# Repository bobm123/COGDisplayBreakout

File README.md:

# COG Display Breakout

This is a breakout board for the **ERC12864FSF-11** COG (Chip On Glass) LCD module, a 0.96", 128x64 pixel display using an ST7567 controller and 4-wire SPI an interface. The PCB routes the display's inputs from its 12-pin FFC cable to a breadboard-friendly 2.54mm pin header. It also exposes the backlight LED pins and provides a few discrete components for LCD module.

It was designed to have a  form factor (~27x27mm, 4 mounting holes, pin headers) to like the Adafruit [0.96" OLED module](https://www.adafruit.com/product/326) and similar 1" displays.

LCD technology differs from the OLED displays commonly found on display boards of this size. LCD should be daylight readable like e-paper, but with simpler hardware and software requirements. However, LCDs may need a backlight in low-light conditions, so the breakout includes connections display's built-in LED with an option for always on operation. Contrast control is through software.

## Specifications

| Parameter | Value |
|-----------|-------|
| Display | [ERC12864FSF-11](https://www.buydisplay.com/0-96-inch-low-cost-white-128x64-graphic-cog-lcd-display-st7567-spi) (128x64, monochrome) |
| Controller | ST7567 |
| Interface | 4-wire SPI |
| Supply voltage | 3.3V only |
| Board size | ~27 x 27mm |
| Mounting | 4x M2 holes |

## Repository Structure

```
ArduinoCode/                             Example sketches for ESP32-C3
COGDisplayBreakout.pretty/               Custom footprint library
COGDisplayBreakout.3dmodels/             Custom 3D models
docs/                                    Datasheets, reference designs, tutorials
images/                                  Image assets
step/                                    3D models of the board and a small case
COGDisplayBreakout.kicad_sch             Schematic
COGDisplayBreakout.kicad_pcb             PCB layout
COGDisplayBreakout.kicad_sym             Custom symbol library
README.md
```

---

## Schematic and Board Layout

The KiCad 9 project files are at the repository root.

### Circuit Overview

The schematic connects the ERC12864FSF-11 display to an 8-pin SPI header (J1) with supporting passives:

**Header pinout (J1 - SPI_Header):**

| Pin | Signal | Description |
|-----|--------|-------------|
| 1 | SDA | SPI data (MOSI) |
| 2 | SCL | SPI clock |
| 3 | A0 | Data/command select (DC) |
| 4 | /RST | Reset (active low) |
| 5 | /CS | Chip select (active low) |
| 6 | LED | LED control |
| 7 | VDD | +3.3V supply |
| 8 | GND | Ground |

**Passive components:**

| Ref | Value | Purpose |
|-----|-------|---------|
| R1 | 20R | Backlight LED current-limiting resistor |
| C1 | 10uF |  VDD bypass capacitor|
| C2 | 100nF | VDD bypass capacitor |
| C3 | 1uF | Charge pump capacitor (V0 to XV0) |
| C4 | 1uF | Charge pump capacitor (V0 to GND) |
| U1 | APX805S | Power-on reset IC for display /RST line |

The ST7567's built-in voltage booster generates the LCD bias voltage using external capacitors C3, and C4. No regulator or level shifting is included; the board is 3.3V only. Capacitors C1 and C2 are for decoupling. The R1 value was taken from the reference design, but for 10-20 mA LED current it should be about 200 Ohms.

The APX805S monitors VDD and holds the display /RST line low until power is stable, providing a clean power-on reset without requiring a GPIO pin from the host microcontroller. The /RST header pin (pin 4) is still available for external reset if needed.

### PCB

This is a 2-layer board, ~27x27mm. The display's 12-pin FFC cable (0.6mm pitch) is soldered directly to SMD pads on the back side. The display module mounts flat against the front by means of plastic mounting pins on the display case and the solder tabs for the backlight LED. Four M2 mounting holes at the corners matching similar OLED modules.

The display's 12-pin FFC cable is a non-standard 0.6mm pitch, so must be soldered directly to pads on the breakout PCB.

PCB Front (ground plane copper hidden)

PCB Back

### Board Revisions

- **V0.1** (March 2026) - Initial prototype. Known issues: C1 wiring error, missing VG capacitor. See `AssemblyNotes.txt` for workarounds.

- **V0.2** (March 2026) - Fixed capacitor circuit. Known issue: backlight A/K pads swapped. See `AssemblyNotes.txt`.
Gerber files: V0.2 in `Gerbers20260323/`.

- **V1.0** (April 2026) - Fixed A/K pads and connected LED control to pin 6. See `AssemblyNotes.txt`.
Gerber files: V1.0 in `Gerbers20260403/`.

- **V1.1** (April 2026) - Added APX805S power-on reset IC for display /RST line. External reset connection via header pin 4 remains optional.
Gerbers sent to DigiKey RedBoard fab 2026-04-15.

---

## Custom ERC12864FSF-11 KiCad Library

The project includes a custom schematic symbol, PCB footprint, and 3D model for the ERC12864FSF-11 display module. These are in project-local libraries referenced via `sym-lib-table` and `fp-lib-table`.

### Schematic Symbol

**File:** `COGDisplayBreakout.kicad_sym`
**Symbol name:** `ERC12864FSF-11`

12-pin FFC cable (0.6mm pitch, 19mm long) plus 2 backlight pins.

| Pin | Name | Type | Description |
|-----|------|------|-------------|
| 1 | ~{CS} | Input | Chip select (active low) |
| 2 | ~{RST} | Input | Reset (active low) |
| 3 | A0 | Input | Data/command select |
| 4 | SCL | Input | SPI clock |
| 5 | SDA | Input | SPI data (MOSI) |
| 6 | VDD | Power | +3.3V supply |
| 7 | VSS | Power | Ground |
| 8 | V0 | Passive | Contrast voltage (booster output) |
| 9 | XV0 | Passive | Booster capacitor tap |
| 10 | NC | - | Not connected |
| 11 | NC | - | Not connected |
| 12 | VG | Passive | Negative voltage for LCD bias |
| A | A | Passive | Backlight LED anode |
| K | K | Passive | Backlight LED cathode |

Note: The backlight pins (A, K) are separate solder tabs on the display module, not part of the 12-pin FFC cable.

### PCB Footprint

**File:** `COGDisplayBreakout.pretty/ERC12864FSF-11_COG_LCD.kicad_mod`

There is a lot going on with this component's footprint:
- 12 SMD pads at 0.6mm pitch for direct-solder FFC cable connection
- Module outline on front silkscreen
- Back silkscreen shows how the FFC cable would wrap around
- 2 through-hole oval pads for backlight pins (A and K)
- Two NPT holes for case aliment studs
- An NPT oval slot to pass the FFC cable to the back of the PCB 

The 12 SMD pads are a bit longer to allow some play when wrapping the FFC cable around to the back. The pads and oval slot are positioned relative to the stud holes and backlight pins so the FFC cable end is centered on the pads. 

Unfortunately, there does not seem to be an FFC/FPC connector available in 12-pin, 6mm pitch so it must be soldered to the PCB. A piece of Kapton tape over the solder joins will provide a bit of strain relief and protection from shorts. 
  
### 3D Model

**Directory:** `COGDisplayBreakout.3dmodels/`

| File | Format | Description |
|------|--------|-------------|
| `ERC12864FSF-11.step` | STEP | Solid body model for KiCad 3D viewer |
| `ERC12864FSF-11_COG_LCD.wrl` | VRML | Lightweight preview model |

The STEP model is referenced by the footprint and renders in KiCad's 3D viewer and to export the PCB with components as a 3D model.

---

## Arduino Code

Example sketches are in `ArduinoCode/`. The code should run on most modern Arduino board variants with sufficient pins and memory. The code currently targets the [**Adafruit QT Py ESP32-C3**](https://www.adafruit.com/product/5405) and uses the **U8g2** graphics library.

### Dependencies

- [U8g2](https://github.com/olikraus/u8g2) - Monochrome graphics library (handles ST7567 initialization, SPI transport, fonts, and drawing)
- SPI (built-in)

Install U8g2 via the Arduino IDE Library Manager.

### Pin Mapping (QT Py ESP32-C3 to breakout header)

| Display Signal | Header Pin | QT Py Pin | ESP32-C3 GPIO |
|----------------|------------|-----------|---------------|
| SCL (clock) | 1 | SCK | 10 |
| SDA (data) | 2 | MO | 7 |
| A0 (DC) | 3 | MI* | 8 |
| /RST | 4 | APX805S on breakout | - |
| /CS | 5 | tied to GND | - |
| LED | 6 | A3 | - |
| GND | 1 | GND | - |
| VDD | 2 | 3V3 | - |

*The MISO pin is repurposed as GPIO since the ERC12864 does not provide data out.

### Sketches

Here are some Arduino sketches that can be run on a XIAO style board like Adafruit's QT Py ESP32-C3 with the connections shown above

| Sketch | Description |
|--------|-------------|
| `ERC12864_Hello/` | Minimal hello-world with text and simple graphics. Also blinks the QT Py's NeoPixel. |
| `ERC12864_SPIDemo/` | AI Port of the manufacturer's C tutorial. Cycles through text, graphics primitives, XBM bitmap, and test patterns. Includes commented-out contrast adjustment code for future button support. |
| `GraphicsTest/` | U8g2 graphics test suite (from the U8g2 examples, configured for this display). |
| `ScrollingText/` | U8g2 scrolling text demo (from the U8g2 examples, configured for this display). |

### U8g2 Constructor

All sketches use the same U8g2 constructor. Identifies the display module by part number and the SPI interface pins. See mappings above.

```cpp
U8G2_ST7565_ERC12864_ALT_F_4W_SW_SPI u8g2(U8G2_R0,
    /* clock=*/ 10, /* data=*/ 7, /* cs=*/ U8X8_PIN_NONE, /* dc=*/ 8, /* reset=*/ U8X8_PIN_NONE);
```

- `ERC12864_ALT` - contrast-improved variant for this display
- `_F_` - full framebuffer mode (~1KB RAM)
- `4W_SW_SPI` - 4-wire software SPI

The 4-wire HW variants of the U8g2 constructors are intended for the platform's native SPI interface: MOSI, MISO, clock and chip select. Since this device is write only the MISO pin is repurposed for A0 (Data/Command select). The 4-wire SW constructor is used to support this pin mapping but others are possible.

/CS is tied to GND on the breakout board, so the display is always selected and no GPIO is needed for chip select. If sharing the SPI bus with other devices, connect /CS to a GPIO pin and replace `U8X8_PIN_NONE` with that pin number in the constructor.

/RST is managed by the on-board APX805S power-on reset IC, so no GPIO is needed for reset. If external reset control is required, connect the /RST header pin to a GPIO and replace the reset `U8X8_PIN_NONE` with that pin number.

---

## Reference Documentation

Datasheets and reference material are in `docs/`:

- `ERC12864-11_Datasheet.pdf` - Display module datasheet
- `ST7567_V1.7.pdf` - Controller IC datasheet
- `ERC12864FSF-11_Display.md` - Display specifications summary
- `ERC12864FSF-11_SPI_Reference_Design.md` - Wiring guide and U8g2 examples
- `ERC12864-11_Tutorial/` - Manufacturer's C code tutorial and interface schematic

## Tools

- **KiCad 9** for schematic and PCB design
- **Arduino IDE** with ESP32 board support for firmware development
- **U8g2** library for display graphics

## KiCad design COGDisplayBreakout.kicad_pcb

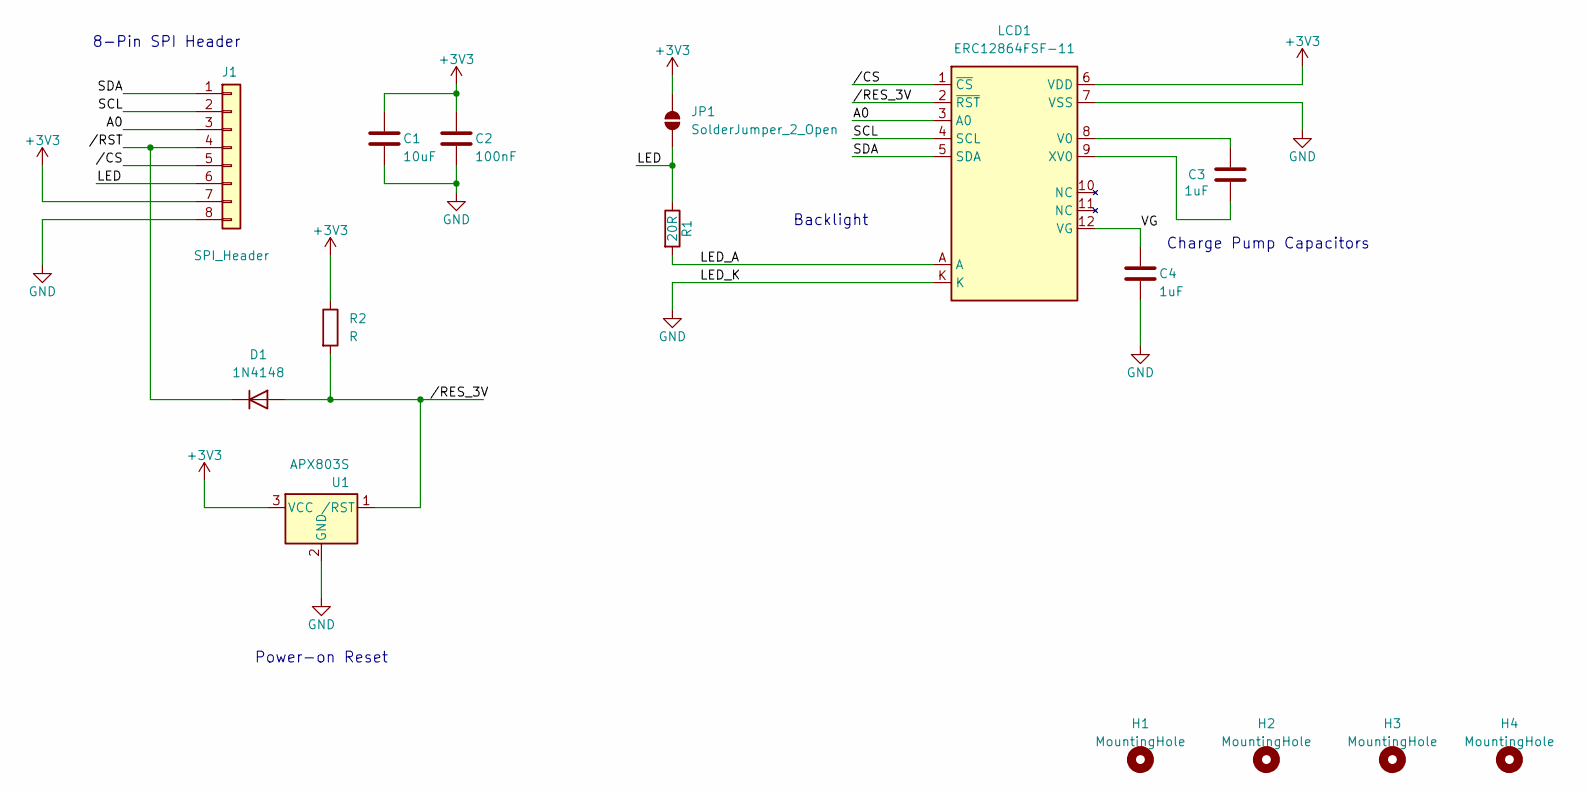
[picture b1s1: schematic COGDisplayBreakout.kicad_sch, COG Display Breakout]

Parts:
C1: 10uF; C_0805_2012Metric_Pad1.18x1.45mm_HandSolder
C2: 100nF; C_0805_2012Metric_Pad1.18x1.45mm_HandSolder
C3, C4: 1uF; C_0805_2012Metric_Pad1.18x1.45mm_HandSolder
D1: 1N4148; D_0805_2012Metric_Pad1.15x1.40mm_HandSolder
H1, H2, H3, H4: MountingHole; MountingHole_2.5mm
J1: SPI_Header; PinHeader_1x08_P2.54mm_Vertical
JP1: SolderJumper_2_Open; SolderJumper-2_P1.3mm_Open_RoundedPad1.0x1.5mm
LCD1: ERC12864FSF-11; ERC12864FSF-11_COG_LCD
R1: 20R; R_0805_2012Metric_Pad1.20x1.40mm_HandSolder
R2: R; R_0805_2012Metric_Pad1.20x1.40mm_HandSolder
U1: APX803S; TSOT-23

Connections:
+3V3: C1.1, C2.1, J1.7, JP1.2 (B), LCD1.6 (VDD), R2.1, U1.3 (VCC)
/A0: J1.3, LCD1.3 (A0)
/LED: J1.6, JP1.1 (A), R1.1
/LED_A: LCD1.A, R1.2
/SCL: J1.2, LCD1.4 (SCL)
/SDA: J1.1, LCD1.5 (SDA)
/VG: C4.1, LCD1.12 (VG)
//CS: J1.5, LCD1.1 (~CS)
//RES_3V: D1.2 (A), LCD1.2 (~RST), R2.2, U1.1 (/RST)
//RST: D1.1 (K), J1.4
GND: C1.2, C2.2, C4.2, J1.8, LCD1.7 (VSS), LCD1.K, U1.2 (GND)
unnamed: C3.1, LCD1.8 (V0)
unnamed: C3.2, LCD1.9 (XV0)

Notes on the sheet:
Charge Pump Capacitors
8-Pin SPI Header
Backlight
Power-on Reset

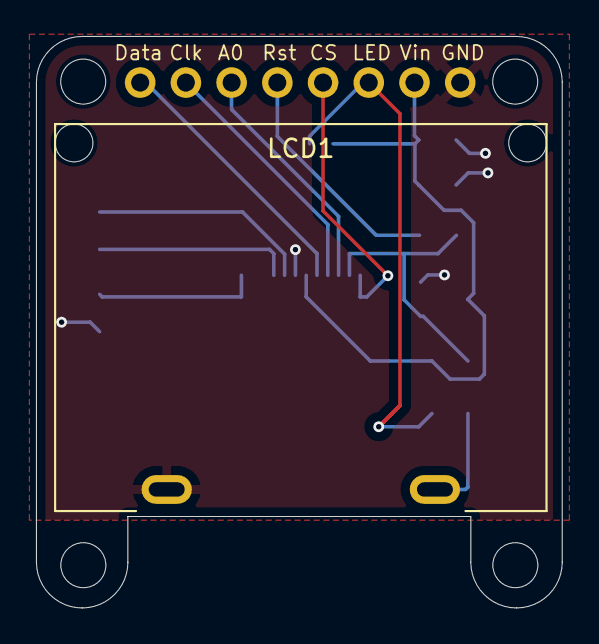
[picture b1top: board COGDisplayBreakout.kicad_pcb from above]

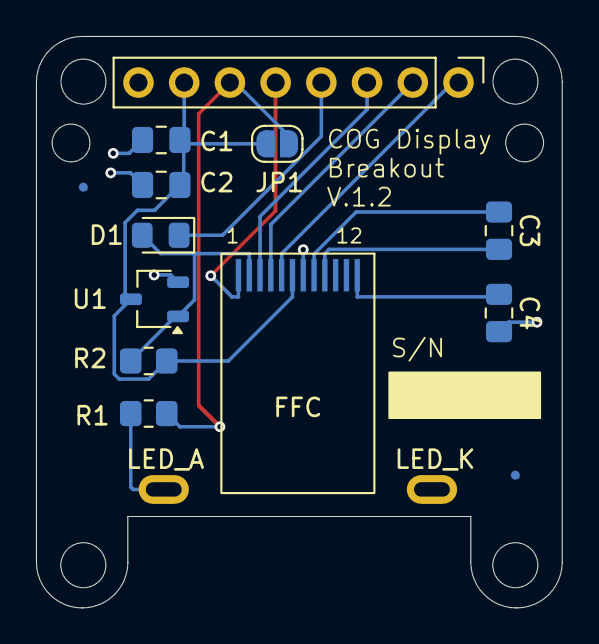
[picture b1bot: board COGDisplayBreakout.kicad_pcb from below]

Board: 2 copper layers, 29.2 x 31.8 mm, 17 parts (12 on the bottom side), 13 nets.

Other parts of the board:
FID1, FID2: FIDUCIAL""; Fiducial_0.5mm_Mask1.5mm

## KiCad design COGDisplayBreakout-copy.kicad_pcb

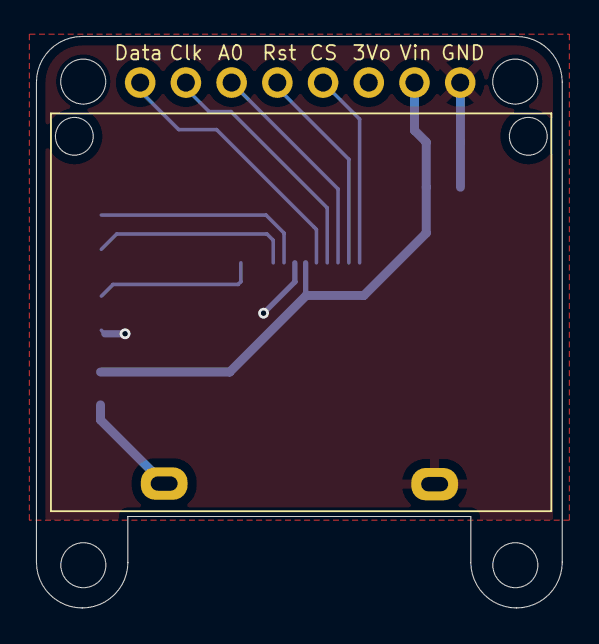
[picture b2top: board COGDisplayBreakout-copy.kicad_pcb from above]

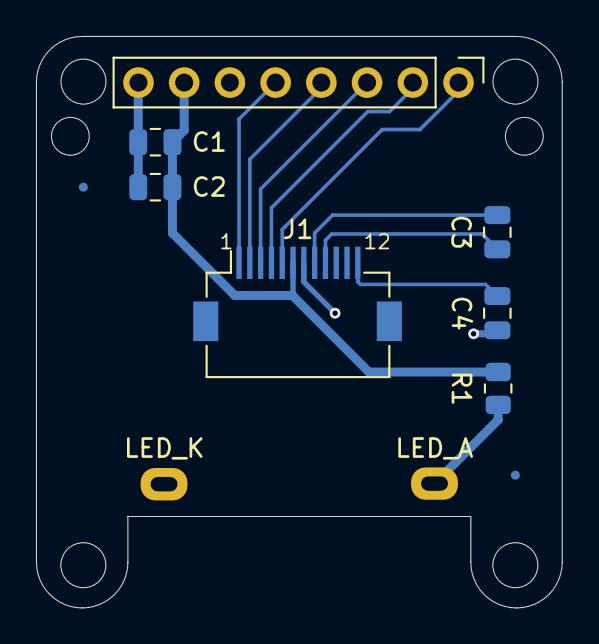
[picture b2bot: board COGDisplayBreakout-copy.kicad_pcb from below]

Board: 2 copper layers, 29.2 x 31.8 mm, 15 parts (11 on the bottom side), 11 nets.

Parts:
C1: 10uF; C_0805_2012Metric
C2: 100nF; C_0805_2012Metric
C3, C4: 1uF; C_0805_2012Metric
FID1, FID2: FIDUCIAL""; Fiducial_0.5mm_Mask1.5mm
H1, H2, H3, H4: MountingHole; MountingHole_2.5mm
J1: FPC_12pin; FFC_SolderPads12pos_x_0.60mm_Horizontal
J2: SPI_Header; PinHeader_1x08_P2.54mm_Vertical
J4, J5: Conn_01x01; PinHeader_1x01_P2.54mm_Oblong
R1: 20R; R_0805_2012Metric

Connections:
+3V3: C1.1, C2.1, J1.6, J2.7, R1.1
/A0: J1.3, J2.3
/LED_A: J4.1, R1.2
/SCL: J1.4, J2.2
/SDA: J1.5, J2.1
/V0: C3.1, J1.8
/VG: C4.1, J1.12
/XV0: C3.2, J1.9
//CS: J1.1, J2.5
//RST: J1.2, J2.4
GND: C1.2, C2.2, C4.2, J1.7, J2.8, J5.1

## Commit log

2026-03-04 Initial Commit of COG breakout board with SPI interface
2026-03-25 3rd Rev send to OshPark
2026-03-26 Adds a footprint and symbol for the ERC12864FSF-11
2026-03-26 Adds a 3D model for the ERC12864FSF-11
2026-03-26 Some adjustments to the ERC12864 3D model
2026-04-02 Notes on the v0.2 boards
2026-04-02 Adds a case based on v0.2 board outline
2026-04-02 Adds the gerbers for v0.2 and some example code
2026-04-02 Adds documentation from the BuyDisplay website
2026-04-02 Adds a readme
2026-04-02 Fixes v0.2 problems, new symbol and 3D model
2026-04-03 Rewired LED: fix A/K swap and adds control from pin 6
2026-04-03 Sent to fab 04/03/2026
2026-04-04 Ensure Handsolder 0805 footprints
2026-04-04 readme edits
2026-04-04 Fixes head pin names and adds some links
2026-04-04 passive refs and functions
2026-04-04 Adds a screen grab of schematic and PCB
2026-04-04 Readme edits and directory cleanup
2026-04-08 Adds a 3D model of a bezel
2026-04-12 Removes /CS line (tied low) from test code
2026-04-12 Adds power on reset
2026-04-12 Some project cleanup after a sketchy merge
2026-04-16 new board layout for power-on reset
2026-04-16 Power-on reset info for readme
2026-04-18 Removes FFC slot (NPTH) from drillings
2026-04-20 Updates some images
2026-05-18 Adds a SN field and label text, v1.2
